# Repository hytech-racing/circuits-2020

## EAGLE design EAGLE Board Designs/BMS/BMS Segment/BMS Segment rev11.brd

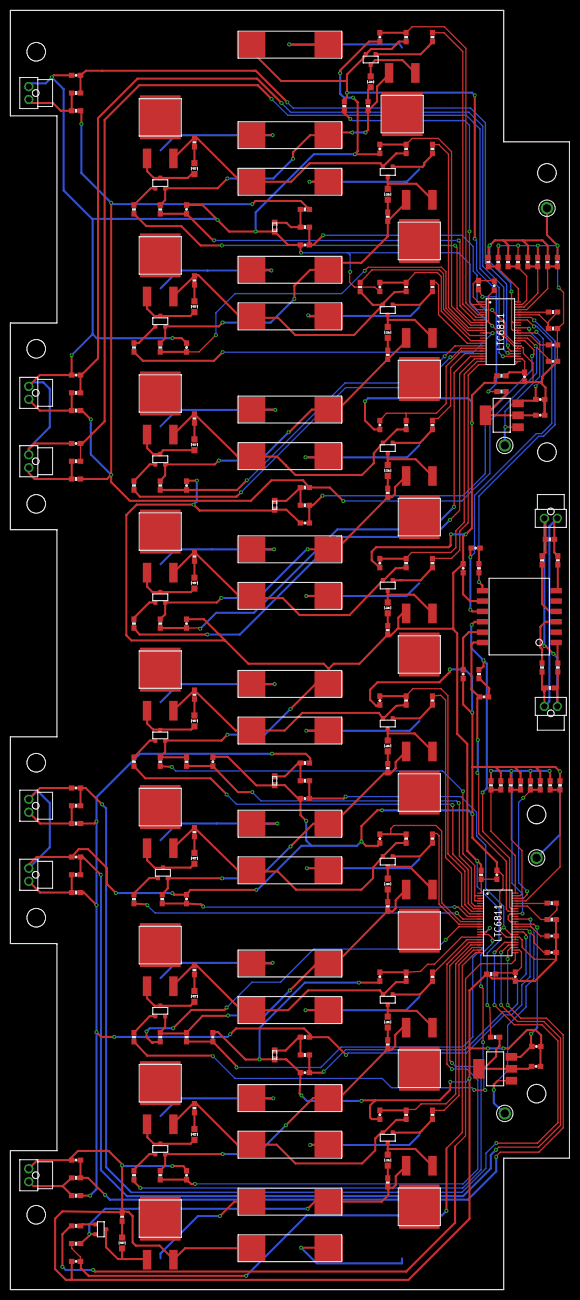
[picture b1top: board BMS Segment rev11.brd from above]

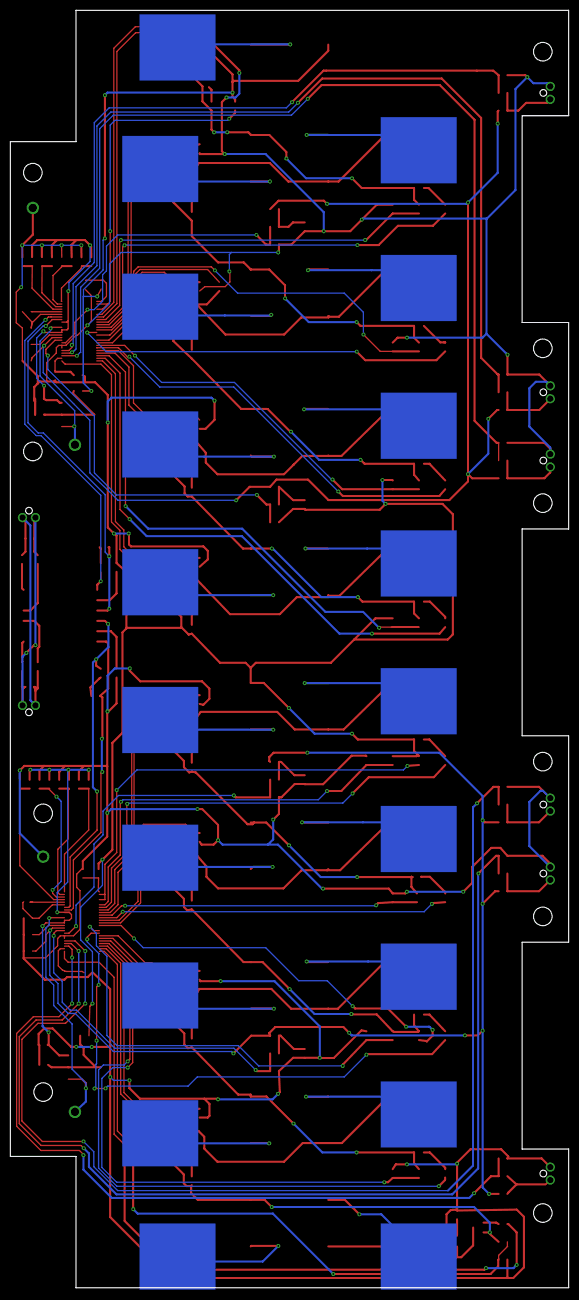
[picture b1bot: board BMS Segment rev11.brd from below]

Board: 2 copper layers, 108.0 x 247.1 mm, 269 parts (19 on the bottom side), 192 nets.

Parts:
C1_A, C1_B, C2_A, C2_B, C8_A, C8_B: 1uF; 0603-CAP
C3_A, C3_B: 15pF; 0603-CAP
C4_A, C4_B, C5_A: 10nF; 0603-CAP
C6_A, C6_B, C7_A, C7_B: 100nF; 0603-CAP
CELL0, CELL1, CELL2, CELL3, CELL4, CELL5, CELL6, CELL7, CELL8, CELL9, CELL10, CELL11, CELL12, CELL13, CELL14, CELL15, CELL16, CELL17, CELL18: BATTERY_SPRING_KEYSTONE5222; KEYSTONE5222
C_5: 10nF; 0603-CAP
DRAIN1:C, DRAIN2:C, DRAIN3:C, DRAIN4:C, DRAIN5:C, DRAIN6:C, DRAIN7:C, DRAIN8:C, DRAIN9:C, DRAIN10:C, DRAIN11:C, DRAIN12:C, DRAIN13:C, DRAIN14:C, DRAIN15:C, DRAIN16:C, DRAIN17:C, DRAIN18:C: 10nF; 0603-CAP
DRAIN1:DISCHARGE, DRAIN2:DISCHARGE, DRAIN3:DISCHARGE, DRAIN4:DISCHARGE, DRAIN5:DISCHARGE, DRAIN6:DISCHARGE, DRAIN7:DISCHARGE, DRAIN8:DISCHARGE, DRAIN9:DISCHARGE, DRAIN10:DISCHARGE, DRAIN11:DISCHARGE, DRAIN12:DISCHARGE, DRAIN13:DISCHARGE, DRAIN14:DISCHARGE, DRAIN15:DISCHARGE, DRAIN16:DISCHARGE, DRAIN17:DISCHARGE, DRAIN18:DISCHARGE: 5R; PWR163
DRAIN1:GATE, DRAIN2:GATE, DRAIN3:GATE, DRAIN4:GATE, DRAIN5:GATE, DRAIN6:GATE, DRAIN7:GATE, DRAIN8:GATE, DRAIN9:GATE, DRAIN10:GATE, DRAIN11:GATE, DRAIN12:GATE, DRAIN13:GATE, DRAIN14:GATE, DRAIN15:GATE, DRAIN16:GATE, DRAIN17:GATE, DRAIN18:GATE: 3K3; 0603-RES
DRAIN1:LED1, DRAIN2:LED1, DRAIN3:LED1, DRAIN4:LED1, DRAIN5:LED1, DRAIN6:LED1, DRAIN7:LED1, DRAIN8:LED1, DRAIN9:LED1, DRAIN10:LED1, DRAIN11:LED1, DRAIN12:LED1, DRAIN13:LED1, DRAIN14:LED1, DRAIN15:LED1, DRAIN16:LED1, DRAIN17:LED1, DRAIN18:LED1: RED; LED-805
DRAIN1:PFET, DRAIN2:PFET, DRAIN3:PFET, DRAIN4:PFET, DRAIN5:PFET, DRAIN6:PFET, DRAIN7:PFET, DRAIN8:PFET, DRAIN9:PFET, DRAIN10:PFET, DRAIN11:PFET, DRAIN12:PFET, DRAIN13:PFET, DRAIN14:PFET, DRAIN15:PFET, DRAIN16:PFET, DRAIN17:PFET, DRAIN18:PFET: P-CHANNEL_MOSFET_DMP3099L-7; SOT23
DRAIN1:R, DRAIN2:R, DRAIN3:R, DRAIN4:R, DRAIN5:R, DRAIN6:R, DRAIN7:R, DRAIN8:R, DRAIN9:R, DRAIN10:R, DRAIN11:R, DRAIN12:R, DRAIN13:R, DRAIN14:R, DRAIN15:R, DRAIN16:R, DRAIN17:R, DRAIN18:R: 100R; 0603-RES
DRAIN1:R1, DRAIN2:R1, DRAIN3:R1, DRAIN4:R1, DRAIN5:R1, DRAIN6:R1, DRAIN7:R1, DRAIN8:R1, DRAIN9:R1, DRAIN10:R1, DRAIN11:R1, DRAIN12:R1, DRAIN13:R1, DRAIN14:R1, DRAIN15:R1, DRAIN16:R1, DRAIN17:R1, DRAIN18:R1: 150R; 0603-RES
F0, F1, F2, F3, F4, F5, F6, F7, F8, F9, F10, F11, F12, F13, F14, F15, F16, F17, F18: 0001.2704.11; 5X20MM_FUSE
ISOSPI_A: ISOSPI; NANO-FIT_VERTICAL-2
ISOSPI_B: ISOSPI; NANO-FIT_VERTICAL-2
J1_A, J1_B, J2_A, J2_B, J3_A, J3_B, J4_A, J4_B, J5_A, J5_B, J6_A, J6_B, J7_A, J7_B, J8_A, J8_B: 0; 0603-RES
R1_A, R1_B, R2_A, R2_B: 100R; 0603-RES
R3_A, R3_B: 402R; 0603-RES
R4_A, R4_B, R5_A, R5_B: 22R; 0603-RES
RB1_A, RB1_B: 1K2; 0603-RES
RB2_A, RB2_B: 806R; 0603-RES
RIN_A: 100R; 0603-RES
RIN_B: 100R; 0603-RES
RM_A: 100R; 0603-RES
RM_B: 100R; 0603-RES
RU1_A, RU1_B, RU2_A, RU2_B: 100R; 0603-RES
THERM1, THERM2, THERM3, THERM4: 10K; 0603
THERM1_A, THERM1_B, THERM2_A, THERM2_B, THERM3_A, THERM3_B: THERMISTOR; NANO-FIT_VERTICAL-2
THERM_FILTER1:C, THERM_FILTER2:C, THERM_FILTER3:C, THERM_FILTER4:C, THERM_FILTER5:C, THERM_FILTER6:C, THERM_FILTER7:C, THERM_FILTER8:C, THERM_FILTER9:C, THERM_FILTER10:C: 10nF; 0603-CAP
THERM_FILTER1:R, THERM_FILTER2:R, THERM_FILTER3:R, THERM_FILTER4:R, THERM_FILTER5:R, THERM_FILTER6:R, THERM_FILTER7:R, THERM_FILTER8:R, THERM_FILTER9:R, THERM_FILTER10:R: 100R; 0603-RES
THERM_FILTER1:R1, THERM_FILTER2:R1, THERM_FILTER3:R1, THERM_FILTER4:R1, THERM_FILTER5:R1, THERM_FILTER6:R1, THERM_FILTER7:R1, THERM_FILTER8:R1, THERM_FILTER9:R1, THERM_FILTER10:R1: 10K; 0603-RES
TRANSFORMER: HM2102NLT
U$1, U$2: LTC6811-2; LTC6811
U$3, U$4: SOT223
U$5, U$6, U$7, U$8: TEST_POINT

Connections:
C0_A: C5_A.1, R2_A.2, U$1.26
C0_B: C_5.1, R2_B.2, U$2.26
C1_A: DRAIN10:C.1, DRAIN10:R.2, U$1.24
C1_B: DRAIN1:C.1, DRAIN1:R.2, U$2.24
C2_A: DRAIN11:C.1, DRAIN11:R.2, U$1.22
C2_B: DRAIN2:C.1, DRAIN2:R.2, U$2.22
C3_A: DRAIN12:C.1, DRAIN12:R.2, U$1.20
C3_B: DRAIN3:C.1, DRAIN3:R.2, U$2.20
C4_A: DRAIN13:C.1, DRAIN13:R.2, U$1.18
C4_B: DRAIN4:C.1, DRAIN4:R.2, U$2.18
C5_A: DRAIN14:C.1, DRAIN14:R.2, U$1.16
C5_B: DRAIN5:C.1, DRAIN5:R.2, U$2.16
C7_A: DRAIN15:C.1, DRAIN15:R.2, U$1.12
C7_B: DRAIN6:C.1, DRAIN6:R.2, U$2.12
C8_A: DRAIN16:C.1, DRAIN16:R.2, U$1.10
C8_B: DRAIN7:C.1, DRAIN7:R.2, U$2.10
C9_A: DRAIN17:C.1, DRAIN17:R.2, U$1.8
C9_B: DRAIN8:C.1, DRAIN8:R.2, U$2.8
C10_A: DRAIN18:C.1, DRAIN18:R.2, U$1.6
C10_B: DRAIN9:C.1, DRAIN9:R.2, U$2.6
CC0: CELL0.P$1, F0.P$1
CC1: CELL1.P$1, F1.P$1
CC2: CELL2.P$1, F2.P$1
CC3: CELL3.P$1, F3.P$1
CC4: CELL4.P$1, F4.P$1
CC5: CELL5.P$1, F5.P$1
CC6: CELL6.P$1, F6.P$1
CC7: CELL7.P$1, F7.P$1
CC8: CELL8.P$1, F8.P$1
CC9: CELL9.P$1, F9.P$1
CC10: CELL10.P$1, F10.P$1
CC11: CELL11.P$1, F11.P$1
CC12: CELL12.P$1, F12.P$1
CC13: CELL13.P$1, F13.P$1
CC14: CELL14.P$1, F14.P$1
CC15: CELL15.P$1, F15.P$1
CC16: CELL16.P$1, F16.P$1
CC17: CELL17.P$1, F17.P$1
CC18: CELL18.P$1, F18.P$1
DRAIN1:GATE: DRAIN1:GATE.1, DRAIN1:PFET.1
DRAIN1:N$1: DRAIN1:DISCHARGE.1, DRAIN1:LED1.A, DRAIN1:PFET.3
DRAIN1:N$2: DRAIN1:LED1.C, DRAIN1:R1.2
DRAIN2:GATE: DRAIN2:GATE.1, DRAIN2:PFET.1
DRAIN2:N$1: DRAIN2:DISCHARGE.1, DRAIN2:LED1.A, DRAIN2:PFET.3
DRAIN2:N$2: DRAIN2:LED1.C, DRAIN2:R1.2
DRAIN3:GATE: DRAIN3:GATE.1, DRAIN3:PFET.1
DRAIN3:N$1: DRAIN3:DISCHARGE.1, DRAIN3:LED1.A, DRAIN3:PFET.3
DRAIN3:N$2: DRAIN3:LED1.C, DRAIN3:R1.2
DRAIN4:GATE: DRAIN4:GATE.1, DRAIN4:PFET.1
DRAIN4:N$1: DRAIN4:DISCHARGE.1, DRAIN4:LED1.A, DRAIN4:PFET.3
DRAIN4:N$2: DRAIN4:LED1.C, DRAIN4:R1.2
DRAIN5:GATE: DRAIN5:GATE.1, DRAIN5:PFET.1
DRAIN5:N$1: DRAIN5:DISCHARGE.1, DRAIN5:LED1.A, DRAIN5:PFET.3
DRAIN5:N$2: DRAIN5:LED1.C, DRAIN5:R1.2
DRAIN6:GATE: DRAIN6:GATE.1, DRAIN6:PFET.1
DRAIN6:N$1: DRAIN6:DISCHARGE.1, DRAIN6:LED1.A, DRAIN6:PFET.3
DRAIN6:N$2: DRAIN6:LED1.C, DRAIN6:R1.2
DRAIN7:GATE: DRAIN7:GATE.1, DRAIN7:PFET.1
DRAIN7:N$1: DRAIN7:DISCHARGE.1, DRAIN7:LED1.A, DRAIN7:PFET.3
DRAIN7:N$2: DRAIN7:LED1.C, DRAIN7:R1.2
DRAIN8:GATE: DRAIN8:GATE.1, DRAIN8:PFET.1
DRAIN8:N$1: DRAIN8:DISCHARGE.1, DRAIN8:LED1.A, DRAIN8:PFET.3
DRAIN8:N$2: DRAIN8:LED1.C, DRAIN8:R1.2
DRAIN9:GATE: DRAIN9:GATE.1, DRAIN9:PFET.1
DRAIN9:N$1: DRAIN9:DISCHARGE.1, DRAIN9:LED1.A, DRAIN9:PFET.3
DRAIN9:N$2: DRAIN9:LED1.C, DRAIN9:R1.2
DRAIN10:GATE: DRAIN10:GATE.1, DRAIN10:PFET.1
DRAIN10:N$1: DRAIN10:DISCHARGE.1, DRAIN10:LED1.A, DRAIN10:PFET.3
DRAIN10:N$2: DRAIN10:LED1.C, DRAIN10:R1.2
DRAIN11:GATE: DRAIN11:GATE.1, DRAIN11:PFET.1
DRAIN11:N$1: DRAIN11:DISCHARGE.1, DRAIN11:LED1.A, DRAIN11:PFET.3
DRAIN11:N$2: DRAIN11:LED1.C, DRAIN11:R1.2
DRAIN12:GATE: DRAIN12:GATE.1, DRAIN12:PFET.1
DRAIN12:N$1: DRAIN12:DISCHARGE.1, DRAIN12:LED1.A, DRAIN12:PFET.3
DRAIN12:N$2: DRAIN12:LED1.C, DRAIN12:R1.2
DRAIN13:GATE: DRAIN13:GATE.1, DRAIN13:PFET.1
DRAIN13:N$1: DRAIN13:DISCHARGE.1, DRAIN13:LED1.A, DRAIN13:PFET.3
DRAIN13:N$2: DRAIN13:LED1.C, DRAIN13:R1.2
DRAIN14:GATE: DRAIN14:GATE.1, DRAIN14:PFET.1
DRAIN14:N$1: DRAIN14:DISCHARGE.1, DRAIN14:LED1.A, DRAIN14:PFET.3
DRAIN14:N$2: DRAIN14:LED1.C, DRAIN14:R1.2
DRAIN15:GATE: DRAIN15:GATE.1, DRAIN15:PFET.1
DRAIN15:N$1: DRAIN15:DISCHARGE.1, DRAIN15:LED1.A, DRAIN15:PFET.3
DRAIN15:N$2: DRAIN15:LED1.C, DRAIN15:R1.2
DRAIN16:GATE: DRAIN16:GATE.1, DRAIN16:PFET.1
DRAIN16:N$1: DRAIN16:DISCHARGE.1, DRAIN16:LED1.A, DRAIN16:PFET.3
DRAIN16:N$2: DRAIN16:LED1.C, DRAIN16:R1.2
DRAIN17:GATE: DRAIN17:GATE.1, DRAIN17:PFET.1
DRAIN17:N$1: DRAIN17:DISCHARGE.1, DRAIN17:LED1.A, DRAIN17:PFET.3
DRAIN17:N$2: DRAIN17:LED1.C, DRAIN17:R1.2
DRAIN18:GATE: DRAIN18:GATE.1, DRAIN18:PFET.1
DRAIN18:N$1: DRAIN18:DISCHARGE.1, DRAIN18:LED1.A, DRAIN18:PFET.3
DRAIN18:N$2: DRAIN18:LED1.C, DRAIN18:R1.2
DRIVE_A: U$1.38, U$3.1, U$8.P$1
DRIVE_B: U$2.38, U$4.1, U$7.P$1
GPIO1_A: THERM_FILTER6:C.1, THERM_FILTER6:R.1, U$1.27
GPIO1_B: THERM_FILTER1:C.1, THERM_FILTER1:R.1, U$2.27
GPIO2_A: THERM_FILTER7:C.1, THERM_FILTER7:R.1, U$1.28
GPIO2_B: THERM_FILTER2:C.1, THERM_FILTER2:R.1, U$2.28
GPIO3_A: THERM_FILTER8:C.1, THERM_FILTER8:R.1, U$1.29
GPIO3_B: THERM_FILTER3:C.1, THERM_FILTER3:R.1, U$2.29
GPIO4_A: THERM_FILTER9:C.1, THERM_FILTER9:R.1, U$1.32
GPIO4_B: THERM_FILTER4:C.1, THERM_FILTER4:R.1, U$2.32
GPIO5_A: THERM_FILTER10:C.1, THERM_FILTER10:R.1, U$1.33
GPIO5_B: THERM_FILTER5:C.1, THERM_FILTER5:R.1, U$2.33
IM_A: C3_A.2, TRANSFORMER.P$9, U$1.41
IM_B: C3_B.2, TRANSFORMER.P$12, U$2.41
IP_A: R3_A.1, TRANSFORMER.P$7, U$1.42
IP_B: R3_B.1, TRANSFORMER.P$10, U$2.42
ISOSPI-M: ISOSPI_A.P$2, ISOSPI_B.P$2, R5_A.2, R5_B.2, RM_A.2, RM_B.2
ISOSPI-P: ISOSPI_A.P$1, ISOSPI_B.P$1, R4_A.2, R4_B.2, RM_A.1, RM_B.1
unnamed: C4_B.1, TRANSFORMER.P$11
unnamed: RB1_B.2, U$2.44
unnamed: THERM1_B.P$1, THERM_FILTER1:R.2, THERM_FILTER1:R1.2
unnamed: RB1_B.1, RB2_B.2, U$2.43
unnamed: R4_B.1, TRANSFORMER.P$3
unnamed: RB1_A.2, U$1.44
unnamed: R5_B.1, TRANSFORMER.P$1
unnamed: J7_B.1, J8_B.1, U$2.48
unnamed: J5_B.1, J6_B.1, U$2.47
unnamed: C3_B.1, R3_B.2
unnamed: J3_B.1, J4_B.1, U$2.46
unnamed: J1_B.1, J2_B.1, U$2.45
unnamed: THERM1.2, THERM_FILTER5:R.2, THERM_FILTER5:R1.2
unnamed: THERM2_B.P$1, THERM_FILTER2:R.2, THERM_FILTER2:R1.2
unnamed: THERM2.2, THERM_FILTER4:R.2, THERM_FILTER4:R1.2
unnamed: RB1_A.1, RB2_A.2, U$1.43
unnamed: C4_A.1, TRANSFORMER.P$8
unnamed: R4_A.1, TRANSFORMER.P$6
unnamed: R5_A.1, TRANSFORMER.P$4
unnamed: C3_A.1, R3_A.2
unnamed: THERM3_B.P$1, THERM_FILTER3:R.2, THERM_FILTER3:R1.2
unnamed: J7_A.1, J8_A.1, U$1.48
unnamed: J5_A.1, J6_A.1, U$1.47
unnamed: J3_A.1, J4_A.1, U$1.46
unnamed: J1_A.1, J2_A.1, U$1.45
unnamed: THERM4.2, THERM_FILTER9:R.2, THERM_FILTER9:R1.2
unnamed: THERM3_A.P$1, THERM_FILTER8:R.2, THERM_FILTER8:R1.2
unnamed: THERM3.2, THERM_FILTER10:R.2, THERM_FILTER10:R1.2
unnamed: THERM2_A.P$1, THERM_FILTER7:R.2, THERM_FILTER7:R1.2
unnamed: THERM1_A.P$1, THERM_FILTER6:R.2, THERM_FILTER6:R1.2
S1_A: DRAIN10:GATE.2, U$1.25
S1_B: DRAIN1:GATE.2, U$2.25
S2_A: DRAIN11:GATE.2, U$1.23
S2_B: DRAIN2:GATE.2, U$2.23
S3_A: DRAIN12:GATE.2, U$1.21
S3_B: DRAIN3:GATE.2, U$2.21
S4_A: DRAIN13:GATE.2, U$1.19
S4_B: DRAIN4:GATE.2, U$2.19
S5_A: DRAIN14:GATE.2, U$1.17
S5_B: DRAIN5:GATE.2, U$2.17
S7_A: DRAIN15:GATE.2, U$1.13
S7_B: DRAIN6:GATE.2, U$2.13
S8_A: DRAIN16:GATE.2, U$1.11
S8_B: DRAIN7:GATE.2, U$2.11
S9_A: DRAIN17:GATE.2, U$1.9
S9_B: DRAIN8:GATE.2, U$2.9
S10_A: DRAIN18:GATE.2, U$1.7
S10_B: DRAIN9:GATE.2, U$2.7
SENSE1: DRAIN1:PFET.2, DRAIN1:R.1, DRAIN2:DISCHARGE.2, DRAIN2:R1.1, F1.P$2
SENSE2: DRAIN2:PFET.2, DRAIN2:R.1, DRAIN3:DISCHARGE.2, DRAIN3:R1.1, F2.P$2
SENSE3: DRAIN3:PFET.2, DRAIN3:R.1, DRAIN4:DISCHARGE.2, DRAIN4:R1.1, F3.P$2
SENSE4: DRAIN4:PFET.2, DRAIN4:R.1, DRAIN5:DISCHARGE.2, DRAIN5:R1.1, F4.P$2
SENSE5: DRAIN5:PFET.2, DRAIN5:R.1, DRAIN6:DISCHARGE.2, DRAIN6:R1.1, F5.P$2, RU2_B.1
SENSE6: DRAIN6:PFET.2, DRAIN6:R.1, DRAIN7:DISCHARGE.2, DRAIN7:R1.1, F6.P$2
SENSE7: DRAIN7:PFET.2, DRAIN7:R.1, DRAIN8:DISCHARGE.2, DRAIN8:R1.1, F7.P$2
SENSE8: DRAIN8:PFET.2, DRAIN8:R.1, DRAIN9:DISCHARGE.2, DRAIN9:R1.1, F8.P$2
SENSE10: DRAIN10:PFET.2, DRAIN10:R.1, DRAIN11:DISCHARGE.2, DRAIN11:R1.1, F10.P$2
SENSE11: DRAIN11:PFET.2, DRAIN11:R.1, DRAIN12:DISCHARGE.2, DRAIN12:R1.1, F11.P$2
SENSE12: DRAIN12:PFET.2, DRAIN12:R.1, DRAIN13:DISCHARGE.2, DRAIN13:R1.1, F12.P$2
SENSE13: DRAIN13:PFET.2, DRAIN13:R.1, DRAIN14:DISCHARGE.2, DRAIN14:R1.1, F13.P$2
SENSE14: DRAIN14:PFET.2, DRAIN14:R.1, DRAIN15:DISCHARGE.2, DRAIN15:R1.1, F14.P$2, RU2_A.1
SENSE15: DRAIN15:PFET.2, DRAIN15:R.1, DRAIN16:DISCHARGE.2, DRAIN16:R1.1, F15.P$2
SENSE16: DRAIN16:PFET.2, DRAIN16:R.1, DRAIN17:DISCHARGE.2, DRAIN17:R1.1, F16.P$2
SENSE17: DRAIN17:PFET.2, DRAIN17:R.1, DRAIN18:DISCHARGE.2, DRAIN18:R1.1, F17.P$2
SENSE18: DRAIN18:PFET.2, DRAIN18:R.1, F18.P$2, R1_A.1, RIN_A.1, RU1_A.1
UNUSED1_A: RU1_A.2, U$1.2, U$1.4
UNUSED1_B: RU1_B.2, U$2.2, U$2.4
UNUSED2_A: RU2_A.2, U$1.14
UNUSED2_B: RU2_B.2, U$2.14
V+_A: C6_A.1, R1_A.2, U$1.1
V+_B: C6_B.1, R1_B.2, U$2.1
V-_A: C1_A.2, C2_A.2, C4_A.2, C5_A.2, C6_A.2, C7_A.2, C8_A.2, DRAIN9:PFET.2, DRAIN9:R.1, DRAIN10:C.2, DRAIN10:DISCHARGE.2, DRAIN10:R1.1, DRAIN11:C.2, DRAIN12:C.2, DRAIN13:C.2, DRAIN14:C.2, DRAIN15:C.2, DRAIN16:C.2, DRAIN17:C.2, DRAIN18:C.2, F9.P$2, J1_A.2, J3_A.2, J5_A.2, J7_A.2, R1_B.1, R2_A.1, RB2_A.1, RIN_B.1, RU1_B.1, THERM1_A.P$2, THERM2_A.P$2, THERM3.1, THERM3_A.P$2, THERM4.1, THERM_FILTER6:C.2, THERM_FILTER7:C.2, THERM_FILTER8:C.2, THERM_FILTER9:C.2, THERM_FILTER10:C.2, U$1.30, U$1.31, U$5.P$1
V-_B: C1_B.2, C2_B.2, C4_B.2, C6_B.2, C7_B.2, C8_B.2, C_5.2, DRAIN1:C.2, DRAIN1:DISCHARGE.2, DRAIN1:R1.1, DRAIN2:C.2, DRAIN3:C.2, DRAIN4:C.2, DRAIN5:C.2, DRAIN6:C.2, DRAIN7:C.2, DRAIN8:C.2, DRAIN9:C.2, F0.P$2, J1_B.2, J3_B.2, J5_B.2, J7_B.2, R2_B.1, RB2_B.1, THERM1.1, THERM1_B.P$2, THERM2.1, THERM2_B.P$2, THERM3_B.P$2, THERM_FILTER1:C.2, THERM_FILTER2:C.2, THERM_FILTER3:C.2, THERM_FILTER4:C.2, THERM_FILTER5:C.2, U$2.30, U$2.31, U$6.P$1
VIN_A: C7_A.1, RIN_A.2, U$3.2, U$3.4
VIN_B: C7_B.1, RIN_B.2, U$4.2, U$4.4
VREF1_A: C2_A.1, U$1.35
VREF1_B: C2_B.1, U$2.35
VREF2_A: C1_A.1, THERM_FILTER6:R1.1, THERM_FILTER7:R1.1, THERM_FILTER8:R1.1, THERM_FILTER9:R1.1, THERM_FILTER10:R1.1, U$1.34
VREF2_B: C1_B.1, THERM_FILTER1:R1.1, THERM_FILTER2:R1.1, THERM_FILTER3:R1.1, THERM_FILTER4:R1.1, THERM_FILTER5:R1.1, U$2.34
VREG_A: C8_A.1, J2_A.2, J4_A.2, J6_A.2, J8_A.2, U$1.36, U$1.37, U$1.40, U$3.3
VREG_B: C8_B.1, J2_B.2, J4_B.2, J6_B.2, J8_B.2, U$2.36, U$2.37, U$2.40, U$4.3
